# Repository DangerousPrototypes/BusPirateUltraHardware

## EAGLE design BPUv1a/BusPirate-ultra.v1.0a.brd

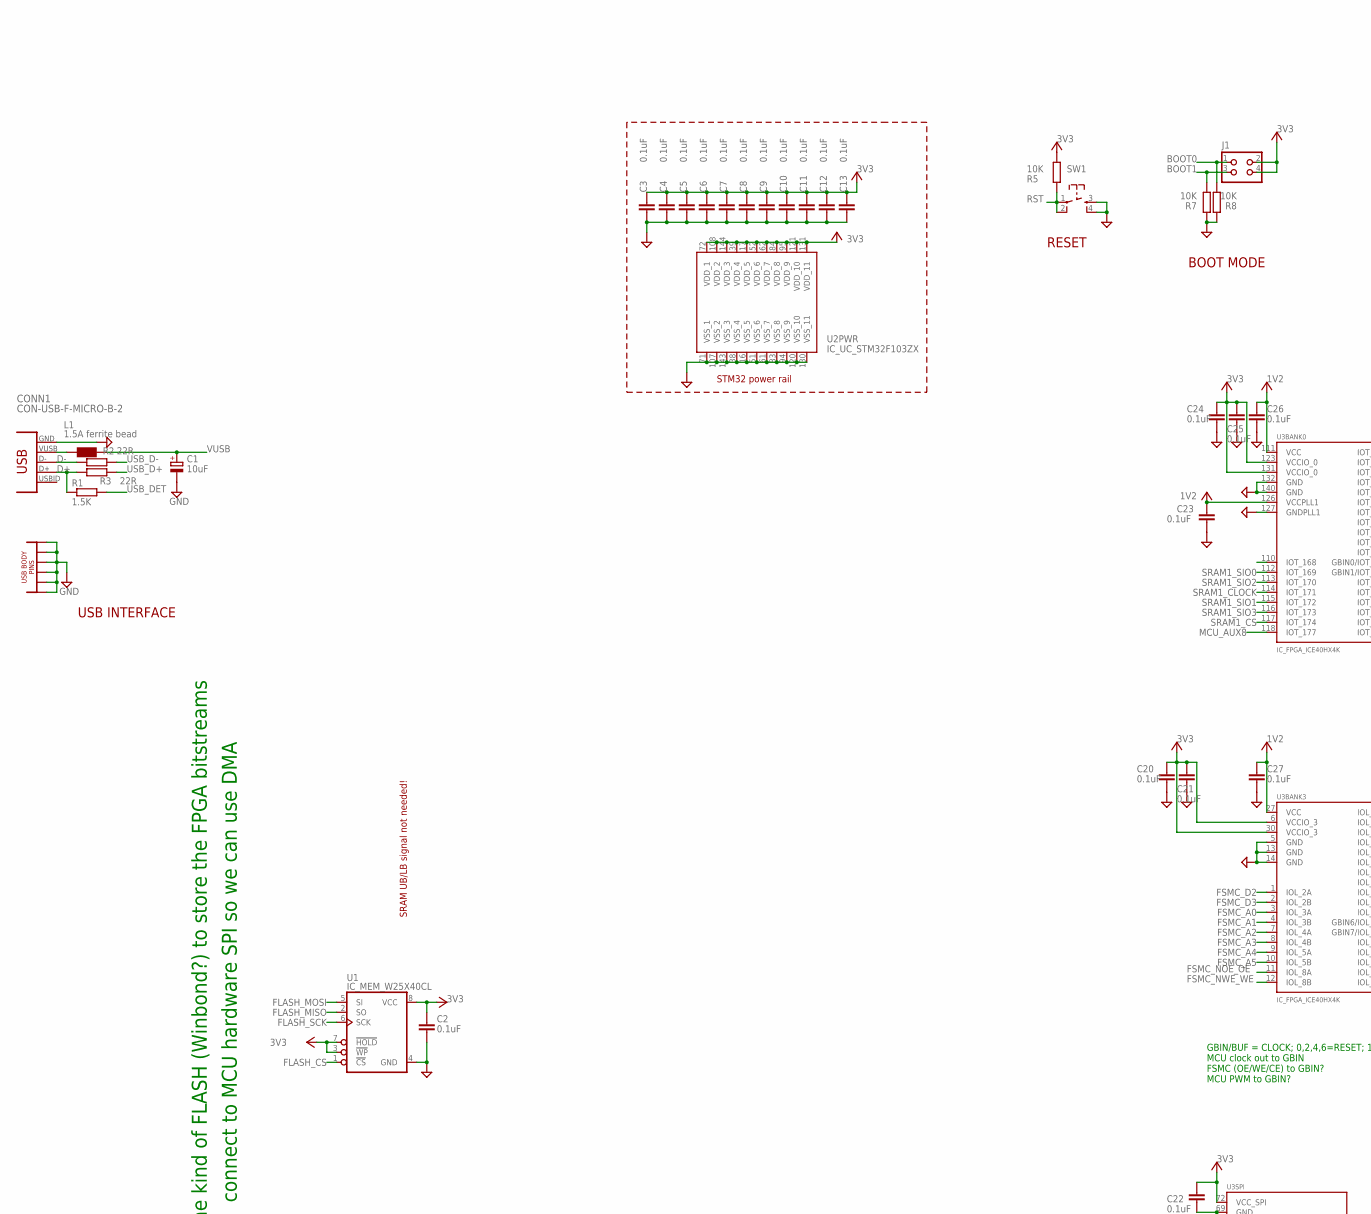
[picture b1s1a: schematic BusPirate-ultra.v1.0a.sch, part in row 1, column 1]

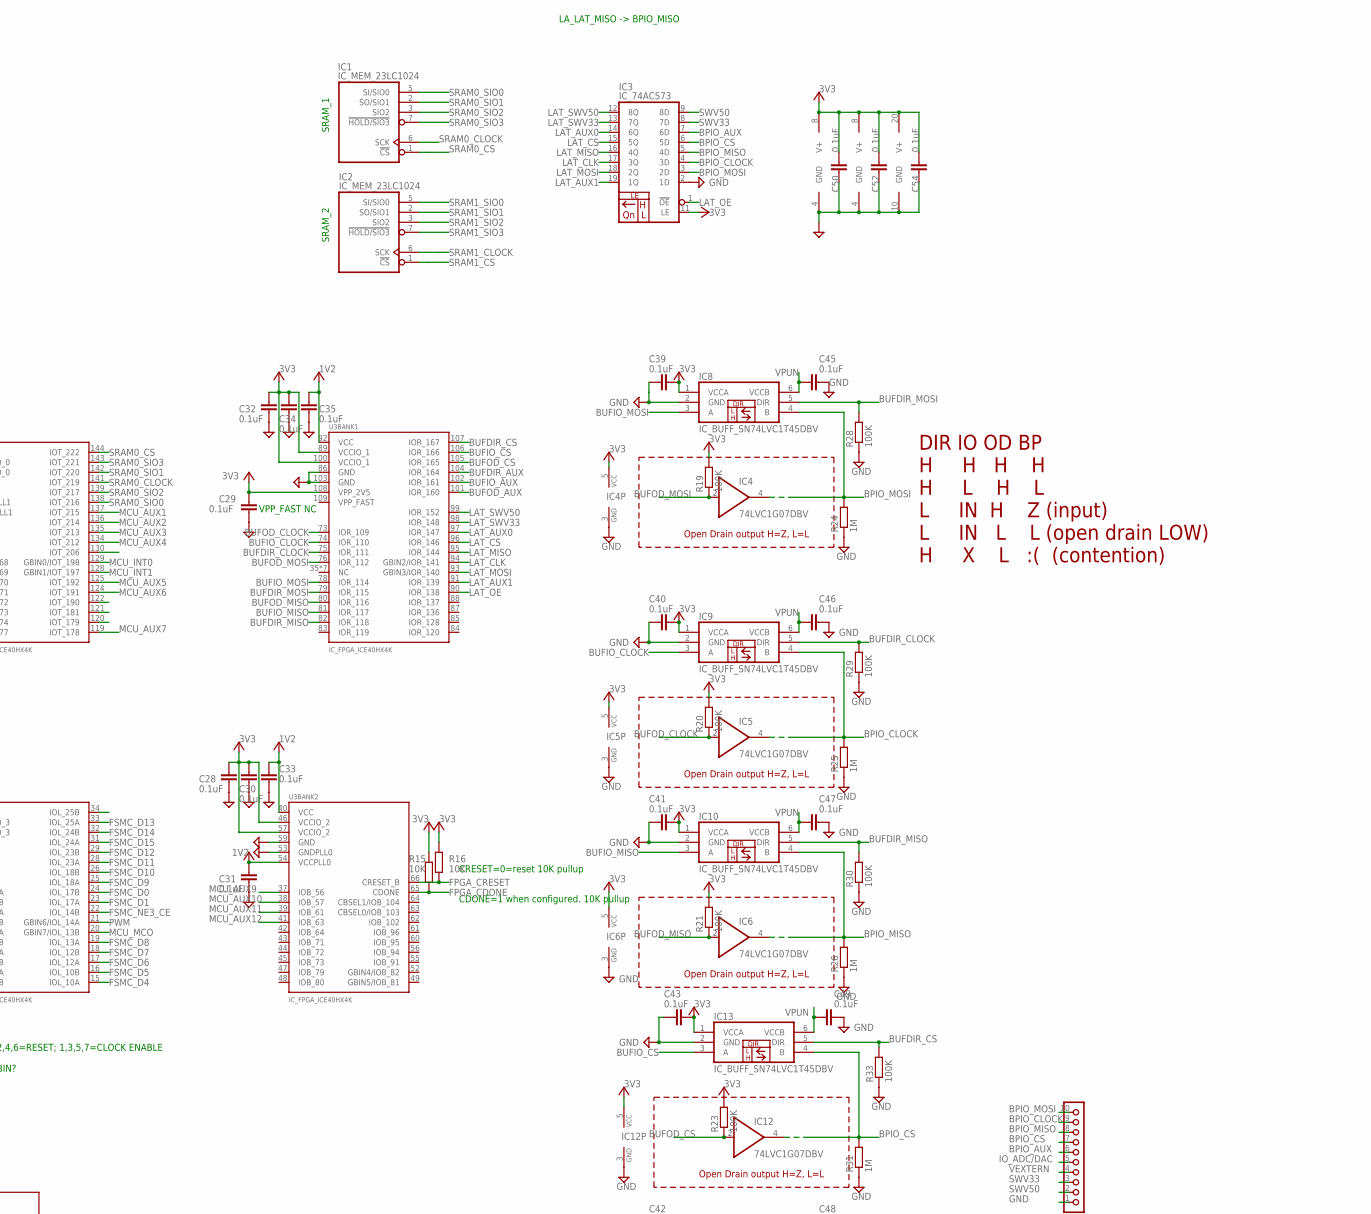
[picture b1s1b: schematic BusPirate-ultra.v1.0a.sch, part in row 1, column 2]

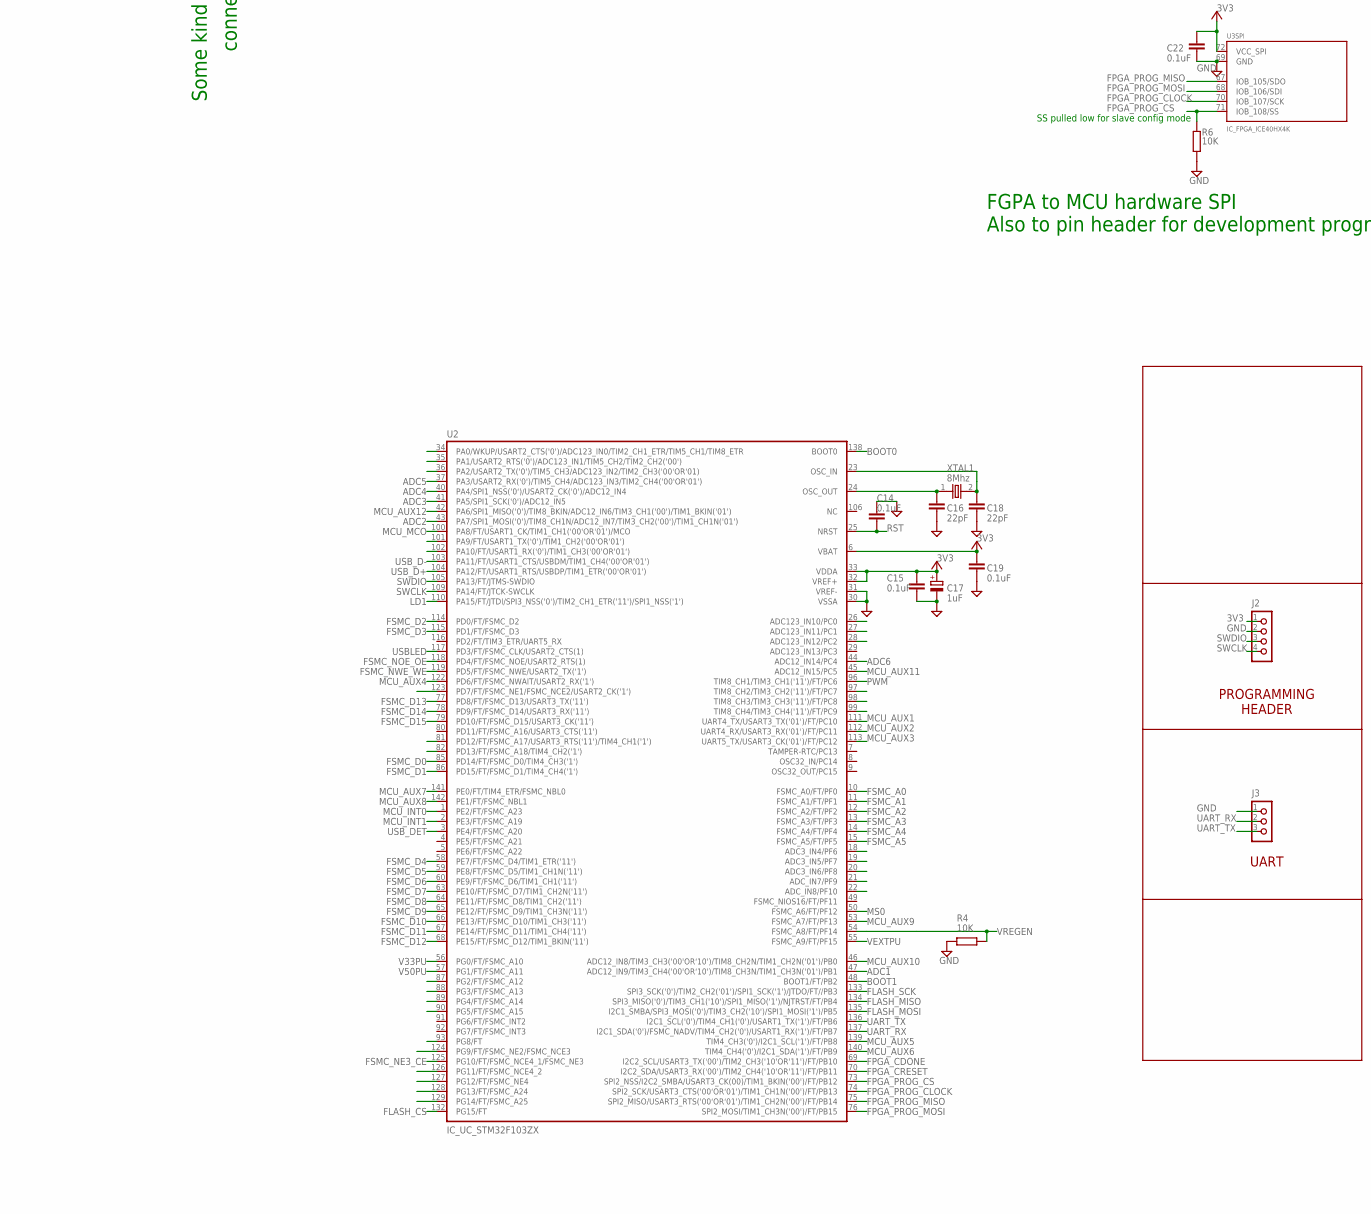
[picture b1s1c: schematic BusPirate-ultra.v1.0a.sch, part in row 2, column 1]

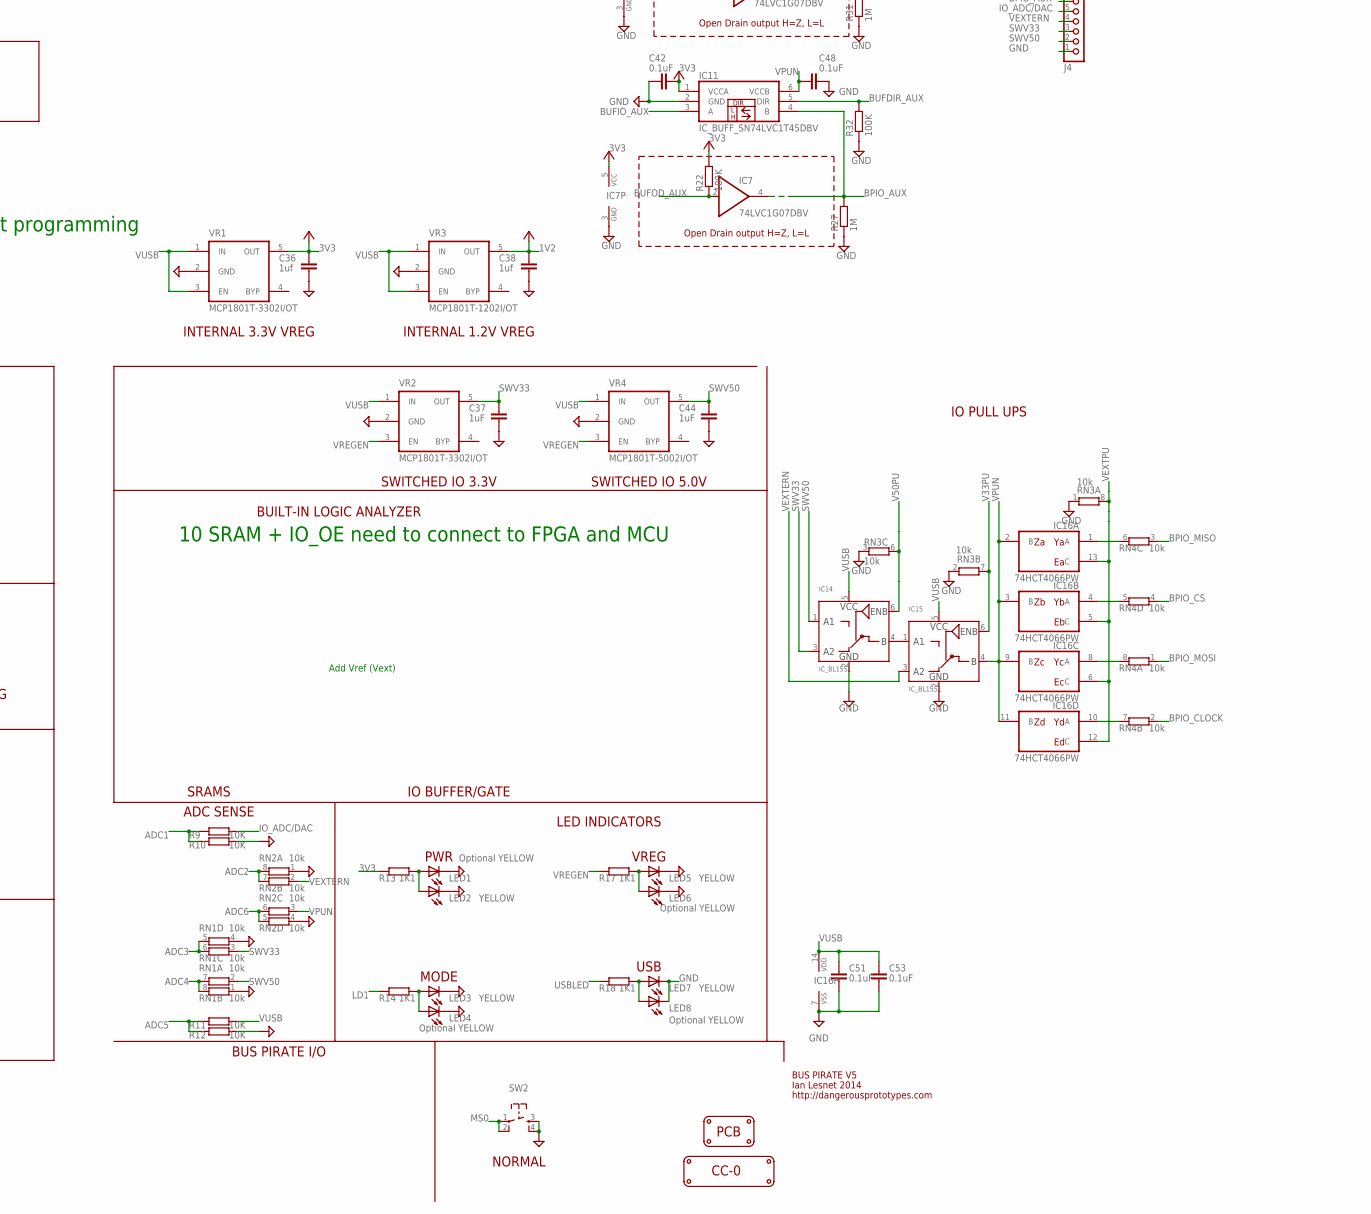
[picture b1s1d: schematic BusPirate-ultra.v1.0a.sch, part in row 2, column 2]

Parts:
C1: 10uF; SMC_A
C2, C3, C4, C5, C6, C7, C8, C9, C11, C12, C13, C14, C15, C19, C21, C22, C23, C24, C25, C26, C28, C29, C30, C31, C32, C33, C34, C35, C39, C40, C41, C42, C43, C45, C46, C47, C48, C49, C50, C51, C52, C53, C54: 0.1uF; C0603
C10, C20, C27: 0.1uF; C402
C16, C18: 22pF; C0603
C17: 1uF; SMC_A
C36, C38: 1uf; C0603
C37, C44: 1uF; C0603
CONN1: CON-USB-F-MICRO-B-2; CON_USB_MICRO-B-2-SD-47589-001
IC1, IC2: IC_MEM_23LC1024; SOIC-8
IC3: IC_74AC573; TSSOP-20
IC4, IC5, IC6, IC7, IC12: 74LVC1G07DBV; SOT23-5
IC8, IC9, IC10, IC11, IC13: IC_BUFF_SN74LVC1T45DBV; DBV-R-PDSO-G6
IC14, IC15: IC_BL1551; SC-70-6
IC16: 74HCT4066PW; 40XX_TSSOP14
J1: CON_HEADER_2X02-PTH; M2X2
J2: CON_HEADER_1X04; M1X4
J3: CON_HEADER_1X03-PTH; M1X3
J4: CON_HEADER_1X10-RIGHT_ANGLED_PTH_SHROUDED; M1X10_MALE_RIGHT_ANGLES_PTH_SHROUDED
L1: 1.5A ferrite bead; WE-KI_0805_B
LED1, LED4, LED6, LED8: Optional YELLOW; LED-805
LED2, LED3, LED5, LED7: YELLOW; LED-805
LOGO1: LOGO_CC-0
PCB1: PCB_DP_RECTANGLE-50X100; DP10050_V1
R1: 1.5K; R603
R2, R3: 22R; R603
R4, R5, R6: 10K; R603
R7, R8, R9, R10, R11, R12, R15, R16: 10K; R0603
R13, R14, R17, R18: 1K1; R603
R19, R20, R21, R22, R23, R28, R29, R30, R32, R33: 100K; R0603
R24, R25, R26, R27, R31: 1M; R0603
RN1, RN2, RN3, RN4: 10k; RN8P-4R-CRA06S
SW1, SW2: SW_TACT_4P; SW_TACT_SMALL
U1: IC_MEM_W25X40CL; SOIC-8
U2: IC_UC_STM32F103ZX; TQFP-144
U3: IC_FPGA_ICE40HX4K; TQFP-144
VR1, VR2: MCP1801T-3302I/OT; SOT-23-5@1
VR3: MCP1801T-1202I/OT; SOT-23-5@1
VR4: MCP1801T-5002I/OT; SOT-23-5@1
XTAL1: 8Mhz; XTAL_4X6

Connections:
1V2: C23.2, C26.2, C27.1, C31.2, C33.2, C35.2, C38.1, U3.27 (VCC), U3.40 (VCC), U3.54 (VCCPLL0), U3.92 (VCC), U3.111 (VCC), U3.126 (VCCPLL1), VR3.5 (OUT)
3V3: C2.2, C3.2, C4.2, C5.2, C6.2, C7.2, C8.2, C9.2, C10.1, C11.2, C12.2, C13.2, C15.2, C17.+, C19.2, C20.1, C21.2, C22.2, C24.2, C25.2, C28.2, C29.2, C30.2, C32.2, C34.2, C36.1, C39.1, C40.1, C41.1, C42.1, C43.1, C50.1, C52.1, C54.1, IC1.8 (V+), IC2.8 (V+), IC3.11 (LE), IC3.20 (V+), IC4.5 (VCC), IC5.5 (VCC), IC6.5 (VCC), IC7.5 (VCC), IC8.1 (VCCA), IC9.1 (VCCA), IC10.1 (VCCA), IC11.1 (VCCA), IC12.5 (VCC), IC13.1 (VCCA), J1.2, J1.4, J2.1, R5.2, R13.2, R15.2, R16.2, R19.2, R20.2, R21.2, R22.2, R23.2, U1.3 (!WP), U1.7 (!HOLD), U1.8 (VCC), U2.6 (VBAT), U2.17 (VDD_5), U2.32 (VREF+), U2.33 (VDDA), U2.39 (VDD_4), U2.52 (VDD_6), U2.62 (VDD_7), U2.72 (VDD_1), U2.84 (VDD_8), U2.95 (VDD_9), U2.108 (VDD_2), U2.121 (VDD_10), U2.131 (VDD_11), U2.144 (VDD_3), U3.6 (VCCIO_3), U3.30 (VCCIO_3), U3.46 (VCCIO_2), U3.57 (VCCIO_2), U3.72 (VCC_SPI), U3.89 (VCCIO_1), U3.100 (VCCIO_1), U3.108 (VPP_2V5), U3.123 (VCCIO_0), U3.131 (VCCIO_0), VR1.5 (OUT)
ADC1: R9.2, R10.2, U2.47 (ADC12_IN9/TIM3_CH4('00'OR'10')/TIM8_CH3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)
ADC2: RN2.7 (2), RN2.8 (2), U2.43 (PA7/SPI1_MOSI('0')/TIM8_CH1N/ADC12_IN7/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)
ADC3: RN1.5 (2), RN1.6 (2), U2.41 (PA5/SPI1_SCK('0')/ADC12_IN5)
ADC4: RN1.7 (2), RN1.8 (2), U2.40 (PA4/SPI1_NSS('0')/USART2_CK('0')/ADC12_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)
ADC5: R11.2, R12.2, U2.37 (PA3/USART2_RX('0')/TIM5_CH4/ADC123_IN3/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)
ADC6: RN2.5 (2), RN2.6 (2), U2.44 (ADC12_IN14/PC4)
BOOT0: J1.1, R8.1, U2.138 (BOOT0)
BOOT1: J1.3, R7.1, U2.48 (BOOT1/FT/PB2)
BPIO_AUX: IC3.7 (6D), IC7.4 (O), IC11.4 (B), J4.6, R27.2
BPIO_CLOCK: IC3.4 (3D), IC5.4 (O), IC9.4 (B), J4.9, R25.2, RN4.2 (1)
BPIO_CS: IC3.6 (5D), IC12.4 (O), IC13.4 (B), J4.7, R31.2, RN4.4 (1)
BPIO_MISO: IC3.5 (4D), IC6.4 (O), IC10.4 (B), J4.8, R26.2, RN4.3 (1)
BPIO_MOSI: IC3.3 (2D), IC4.4 (O), IC8.4 (B), J4.10, R24.2, RN4.1
BUFDIR_AUX: IC11.5 (DIR), R32.2, U3.104 (IOR_164)
BUFDIR_CLOCK: IC9.5 (DIR), R29.2, U3.75 (IOR_111)
BUFDIR_CS: IC13.5 (DIR), R33.2, U3.107 (IOR_167)
BUFDIR_MISO: IC10.5 (DIR), R30.2, U3.82 (IOR_118)
BUFDIR_MOSI: IC8.5 (DIR), R28.2, U3.79 (IOR_115)
BUFIO_AUX: IC11.3 (A), U3.102 (IOR_161)
BUFIO_CLOCK: IC9.3 (A), U3.74 (IOR_110)
BUFIO_CS: IC13.3 (A), U3.106 (IOR_166)
BUFIO_MISO: IC10.3 (A), U3.81 (IOR_117)
BUFIO_MOSI: IC8.3 (A), U3.78 (IOR_114)
BUFOD_AUX: IC7.2 (I), R22.1, U3.101 (IOR_160)
BUFOD_CLOCK: IC5.2 (I), R20.1, U3.73 (IOR_109)
BUFOD_CS: IC12.2 (I), R23.1, U3.105 (IOR_165)
BUFOD_MISO: IC6.2 (I), R21.1, U3.80 (IOR_116)
BUFOD_MOSI: IC4.2 (I), R19.1, U3.76 (IOR_112)
D+: CONN1.P3 (D+), R1.1, R3.2
D-: CONN1.P2 (D-), R2.2
EXVUSB: CONN1.P1 (VUSB), L1.2 (1)
FLASH_CS: U1.1 (!CS), U2.132 (PG15/FT)
FLASH_MISO: U1.2 (SO), U2.134 (SPI3_MISO('0')/TIM3_CH1('10')/SPI1_MISO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)
FLASH_MOSI: U1.5 (SI), U2.135 (I2C1_SMBA/SPI3_MOSI('0')/TIM3_CH2('10')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)
FLASH_SCK: U1.6 (SCK), U2.133 (SPI3_SCK('0')/TIM2_CH2('01')/SPI1_SCK('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)
FPGA_CDONE: R15.1, U2.69 (I2C2_SCL/USART3_TX('00')/TIM2_CH3('10'O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), U3.65 (CDONE)
FPGA_CRESET: R16.1, U2.70 (I2C2_SDA/USART3_RX('00')/TIM2_CH4('10'O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), U3.66 (CRESET_B)
FPGA_PROG_CLOCK: U2.74 (SPI2_SCK/USART3_CTS('00'OR'01')/TIM1_CH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), U3.70 (IOB_107/SCK)
FPGA_PROG_CS: R6.1, U2.73 (SPI2_NSS/I2C2_SMBA/USART3_CK(00)/TIM1_B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), U3.71 (IOB_108/SS)
FPGA_PROG_MISO: U2.75 (SPI2_MISO/USART3_RTS('00'OR'01')/TIM1_C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), U3.67 (IOB_105/SDO)
FPGA_PROG_MOSI: U2.76 (SPI2_MOSI/TIM1_CH3N('00')/FT/PB15), U3.68 (IOB_106/SDI)
FSMC_A0: U2.10 (FSMC_A0/FT/PF0), U3.3 (IOL_3A)
FSMC_A1: U2.11 (FSMC_A1/FT/PF1), U3.4 (IOL_3B)
FSMC_A2: U2.12 (FSMC_A2/FT/PF2), U3.7 (IOL_4A)
FSMC_A3: U2.13 (FSMC_A3/FT/PF3), U3.8 (IOL_4B)
FSMC_A4: U2.14 (FSMC_A4/FT/PF4), U3.9 (IOL_5A)
FSMC_A5: U2.15 (FSMC_A5/FT/PF5), U3.10 (IOL_5B)
FSMC_D0: U2.85 (PD14/FT/FSMC_D0/TIM4_CH3('1')), U3.24 (IOL_17B)
FSMC_D1: U2.86 (PD15/FT/FSMC_D1/TIM4_CH4('1')), U3.23 (IOL_17A)
FSMC_D2: U2.114 (PD0/FT/FSMC_D2), U3.1 (IOL_2A)
FSMC_D3: U2.115 (PD1/FT/FSMC_D3), U3.2 (IOL_2B)
FSMC_D4: U2.58 (PE7/FT/FSMC_D4/TIM1_ETR('11')), U3.15 (IOL_10A)
FSMC_D5: U2.59 (PE8/FT/FSMC_D5/TIM1_CH1N('11')), U3.16 (IOL_10B)
FSMC_D6: U2.60 (PE9/FT/FSMC_D6/TIM1_CH1('11')), U3.17 (IOL_12A)
FSMC_D7: U2.63 (PE10/FT/FSMC_D7/TIM1_CH2N('11')), U3.18 (IOL_12B)
FSMC_D8: U2.64 (PE11/FT/FSMC_D8/TIM1_CH2('11')), U3.19 (IOL_13A)
FSMC_D9: U2.65 (PE12/FT/FSMC_D9/TIM1_CH3N('11')), U3.25 (IOL_18A)
FSMC_D10: U2.66 (PE13/FT/FSMC_D10/TIM1_CH3('11')), U3.26 (IOL_18B)
FSMC_D11: U2.67 (PE14/FT/FSMC_D11/TIM1_CH4('11')), U3.28 (IOL_23A)
FSMC_D12: U2.68 (PE15/FT/FSMC_D12/TIM1_BKIN('11')), U3.29 (IOL_23B)
FSMC_D13: U2.77 (PD8/FT/FSMC_D13/USART3_TX('11')), U3.33 (IOL_25A)
FSMC_D14: U2.78 (PD9/FT/FSMC_D14/USART3_RX('11')), U3.32 (IOL_24B)
FSMC_D15: U2.79 (PD10/FT/FSMC_D15/USART3_CK('11')), U3.31 (IOL_24A)
FSMC_NE3_CE: U2.125 (PG10/FT/FSMC_NCE4_1/FSMC_NE3), U3.22 (IOL_14B)
FSMC_NOE_OE: U2.118 (PD4/FT/FSMC_NOE/USART2_RTS(1)), U3.11 (IOL_8A)
FSMC_NWE_WE: U2.119 (PD5/FT/FSMC_NWE/USART2_TX('1')), U3.12 (IOL_8B)
GND: C1.-, C2.1, C3.1, C4.1, C5.1, C6.1, C7.1, C8.1, C9.1, C10.2, C11.1, C12.1, C13.1, C14.1, C15.1, C16.1, C17.-, C18.1, C19.1, C20.2, C21.1, C22.1, C23.1, C24.1, C25.1, C26.1, C27.2, C28.1, C29.1, C30.1, C31.1, C32.1, C33.1, C34.1, C35.1, C36.2, C37.2, C38.2, C39.2, C40.2, C41.2, C42.2, C43.2, C44.2, C45.1, C46.1, C47.1, C48.1, C49.1, C50.2, C51.2, C52.2, C53.2, C54.2, CONN1.BODY@1, CONN1.BODY@2, CONN1.BODY@3, CONN1.BODY@4, CONN1.BODY@5, CONN1.BODY@6, CONN1.BODY@7, CONN1.BODY@8, CONN1.BODY@9, CONN1.BODY@10, CONN1.P5 (GND), IC1.4 (GND), IC2.4 (GND), IC3.2 (1D), IC3.10 (GND), IC4.3 (GND), IC5.3 (GND), IC6.3 (GND), IC7.3 (GND), IC8.2 (GND), IC9.2 (GND), IC10.2 (GND), IC11.2 (GND), IC12.3 (GND), IC13.2 (GND), IC14.2 (GND), IC15.2 (GND), IC16.7 (VSS), J2.2, J3.1, J4.1, LED1.C, LED2.C, LED3.C, LED4.C, LED5.C, LED6.C, LED7.C, LED8.C, R4.2, R6.2, R7.2, R8.2, R10.1, R12.1, R24.1, R25.1, R26.1, R27.1, R28.1, R29.1, R30.1, R31.1, R32.1, R33.1, RN1.1, RN1.4 (1), RN2.1, RN2.4 (1), RN3.1, RN3.2 (1), RN3.3 (1), SW1.3, SW1.4, SW2.3, SW2.4, U1.4 (GND), U2.16 (VSS_5), U2.30 (VSSA), U2.31 (VREF-), U2.38 (VSS_4), U2.51 (VSS_6), U2.61 (VSS_7), U2.71 (VSS_1), U2.83 (VSS_8), U2.94 (VSS_9), U2.107 (VSS_2), U2.120 (VSS_10), U2.130 (VSS_11), U2.143 (VSS_3), U3.5 (GND), U3.13 (GND), U3.14 (GND), U3.53 (GNDPLL0), U3.59 (GND), U3.69 (GND), U3.86 (GND), U3.103 (GND), U3.127 (GNDPLL1), U3.132 (GND), U3.140 (GND), VR1.2 (GND), VR2.2 (GND), VR3.2 (GND), VR4.2 (GND)
IO_ADC/DAC: J4.5, R9.1
LAT_AUX0: IC3.14 (6Q), U3.97 (IOR_147)
LAT_AUX1: IC3.19 (1Q), U3.91 (IOR_139)
LAT_CLK: IC3.17 (3Q), U3.94 (GBIN2/IOR_141)
LAT_CS: IC3.15 (5Q), U3.96 (IOR_146)
LAT_MISO: IC3.16 (4Q), U3.95 (IOR_144)
LAT_MOSI: IC3.18 (2Q), U3.93 (GBIN3/IOR_140)
LAT_OE: IC3.1 (!OE), U3.90 (IOR_138)
LAT_SWV33: IC3.13 (7Q), U3.98 (IOR_148)
LAT_SWV50: IC3.12 (8Q), U3.99 (IOR_152)
LD1: R14.2, U2.110 (PA15/FT/JTDI/SPI3_NSS('0')/TIM2_CH1_ETR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)
MCU_AUX1: U2.111 (UART4_TX/USART3_TX('01')/FT/PC10), U3.137 (IOT_215)
MCU_AUX2: U2.112 (UART4_RX/USART3_RX('01')/FT/PC11), U3.136 (IOT_214)
MCU_AUX3: U2.113 (UART5_TX/USART3_CK('01')/FT/PC12), U3.135 (IOT_213)
MCU_AUX4: U2.122 (PD6/FT/FSMC_NWAIT/USART2_RX('1')), U3.134 (IOT_212)
MCU_AUX5: U2.139 (TIM4_CH3('0')/I2C1_SCL('1')/FT/PB8), U3.125 (IOT_192)
MCU_AUX6: U2.140 (TIM4_CH4('0')/I2C1_SDA('1')/FT/PB9), U3.124 (IOT_191)
MCU_AUX7: U2.141 (PE0/FT/TIM4_ETR/FSMC_NBL0), U3.119 (IOT_178)
MCU_AUX8: U2.142 (PE1/FT/FSMC_NBL1), U3.118 (IOT_177)
MCU_AUX9: U2.53 (FSMC_A7/FT/PF13), U3.37 (IOB_56)
MCU_AUX10: U2.46 (ADC12_IN8/TIM3_CH3('00'OR'10')/TIM8_CH2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), U3.38 (IOB_57)
MCU_AUX11: U2.45 (ADC12_IN15/PC5), U3.39 (IOB_61)
MCU_AUX12: U2.42 (PA6/SPI1_MISO('0')/TIM8_BKIN/ADC12_IN6/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), U3.41 (IOB_63)
MCU_INT0: U2.1 (PE2/FT/FSMC_A23), U3.129 (GBIN0/IOT_198)
MCU_INT1: U2.2 (PE3/FT/FSMC_A19), U3.128 (GBIN1/IOT_197)
MCU_MCO: U2.100 (PA8/FT/USART1_CK/TIM1_CH1('00'OR'01')/M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), U3.20 (GBIN7/IOL_13B)
MS0: SW2.1, SW2.2, U2.50 (FSMC_A6/FT/PF12)
unnamed: IC14.4 (B), IC15.1 (A1)
unnamed: IC16.1 (A), RN4.6 (2)
unnamed: IC16.4 (A), RN4.5 (2)
unnamed: IC16.8 (A), RN4.8 (2)
unnamed: IC16.10 (A), RN4.7 (2)
unnamed: LED3.A, LED4.A, R14.1
unnamed: LED1.A, LED2.A, R13.1
unnamed: C18.2, U2.23 (OSC_IN), XTAL1.2
unnamed: C16.2, U2.24 (OSC_OUT), XTAL1.1
unnamed: LED7.A, LED8.A, R18.1
unnamed: LED5.A, LED6.A, R17.1
PWM: U2.96 (TIM8_CH1/TIM3_CH1('11')/FT/PC6), U3.21 (GBIN6/IOL_14A)
RST: C14.2, R5.1, SW1.1, SW1.2, U2.25 (NRST)
SRAM0_CLOCK: IC1.6 (SCK), U3.141 (IOT_219)
SRAM0_CS: IC1.1 (!CS), U3.144 (IOT_222)
SRAM0_SIO0: IC1.5 (SI/SIO0), U3.138 (IOT_216)
SRAM0_SIO1: IC1.2 (SO/SIO1), U3.142 (IOT_220)
SRAM0_SIO2: IC1.3 (SIO2), U3.139 (IOT_217)
SRAM0_SIO3: IC1.7 (!HOLD/SIO3), U3.143 (IOT_221)
SRAM1_CLOCK: IC2.6 (SCK), U3.114 (IOT_171)
SRAM1_CS: IC2.1 (!CS), U3.117 (IOT_174)
SRAM1_SIO0: IC2.5 (SI/SIO0), U3.112 (IOT_169)
SRAM1_SIO1: IC2.2 (SO/SIO1), U3.115 (IOT_172)
SRAM1_SIO2: IC2.3 (SIO2), U3.113 (IOT_170)
SRAM1_SIO3: IC2.7 (!HOLD/SIO3), U3.116 (IOT_173)
SWCLK: J2.4, U2.109 (PA14/FT/JTCK-SWCLK)
SWDIO: J2.3, U2.105 (PA13/FT/JTMS-SWDIO)
SWV33: C37.1, IC3.8 (7D), IC14.3 (A2), J4.3, RN1.3 (1), VR2.5 (OUT)
SWV50: C44.1, IC3.9 (8D), IC14.1 (A1), J4.2, RN1.2 (1), VR4.5 (OUT)
UART_RX: J3.2, U2.137 (I2C1_SDA('0')/FSMC_NADV/TIM4_CH2('0')/U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)
UART_TX: J3.3, U2.136 (I2C1_SCL('0')/TIM4_CH1('0')/USART1_TX('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)
USBLED: R18.2, U2.117 (PD3/FT/FSMC_CLK/USART2_CTS(1))
USB_D+: R3.1, U2.104 (PA12/FT/USART1_RTS/USBDP/TIM1_ETR('00'O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)
USB_D-: R2.1, U2.103 (PA11/FT/USART1_CTS/USBDM/TIM1_CH4('00'O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)
USB_DET: R1.2, U2.3 (PE4/FT/FSMC_A20)
V33PU: IC15.6 (ENB), RN3.7 (2), U2.56 (PG0/FT/FSMC_A10)
V50PU: IC14.6 (ENB), RN3.6 (2), U2.57 (PG1/FT/FSMC_A11)
VEXTERN: IC15.3 (A2), J4.4, RN2.2 (1)
VEXTPU: IC16.5 (C), IC16.6 (C), IC16.12 (C), IC16.13 (C), RN3.8 (2), U2.55 (FSMC_A9/FT/PF15)
VPP_FAST: U3.109 (VPP_FAST)
VPUN: C45.2, C46.2, C47.2, C48.2, C49.2, IC8.6 (VCCB), IC9.6 (VCCB), IC10.6 (VCCB), IC11.6 (VCCB), IC13.6 (VCCB), IC15.4 (B), IC16.2 (B), IC16.3 (B), IC16.9 (B), IC16.11 (B), RN2.3 (1)
VREGEN: R4.1, R17.2, U2.54 (FSMC_A8/FT/PF14), VR2.3 (EN), VR4.3 (EN)
VUSB: C1.+, C51.1, C53.1, IC14.5 (VCC), IC15.5 (VCC), IC16.14 (VDD), L1.1 (2), R11.1, VR1.1 (IN), VR1.3 (EN), VR2.1 (IN), VR3.1 (IN), VR3.3 (EN), VR4.1 (IN)

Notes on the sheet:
BUS PIRATE V5
Ian Lesnet 2014
http://dangerousprototypes.com
SRAMS
IO BUFFER/GATE
BUS PIRATE I/O
BOOT MODE
PWR
MODE
VREG
PROGRAMMING HEADER
USB
INTERNAL 3.3V VREG
SWITCHED IO 3.3V
SWITCHED IO 5.0V
BUILT-IN LOGIC ANALYZER
ADC SENSE
USB INTERFACE
NORMAL
RESET
IO PULL UPS
LED INDICATORS
UART
SRAM UB/LB signal not needed!
Open Drain output H=Z, L=L
10 SRAM + IO_OE need to connect to FPGA and MCU
Some kind of FLASH (Winbond?) to store the FPGA bitstreams
connect to MCU hardware SPI so we can use DMA
FGPA to MCU hardware SPI Also to pin header for development programming
SS pulled low for slave config mode
CDONE=1 when configured. 10K pullup
CRESET=0=reset 10K pullup
VPP_FAST NC
GBIN/BUF = CLOCK; 0,2,4,6=RESET; 1,3,5,7=CLOCK ENABLE MCU clock out to GBIN FSMC (OE/WE/CE) to GBIN? MCU PWM to GBIN?
Add Vref (Vext)
DIR IO OD BP H H H H H L H L L IN H Z (input) L IN L L (open drain LOW) H X L :( (contention)
STM32 power rail
INTERNAL 1.2V VREG
SRAM_1
SRAM_2

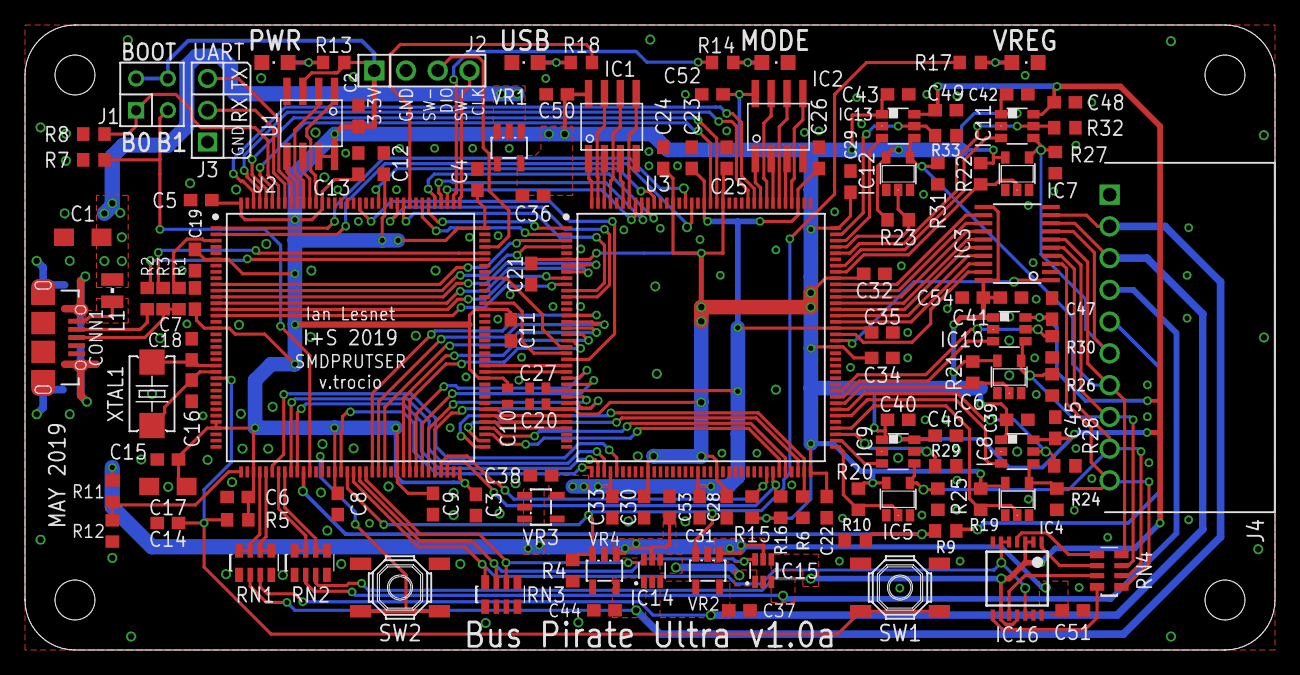
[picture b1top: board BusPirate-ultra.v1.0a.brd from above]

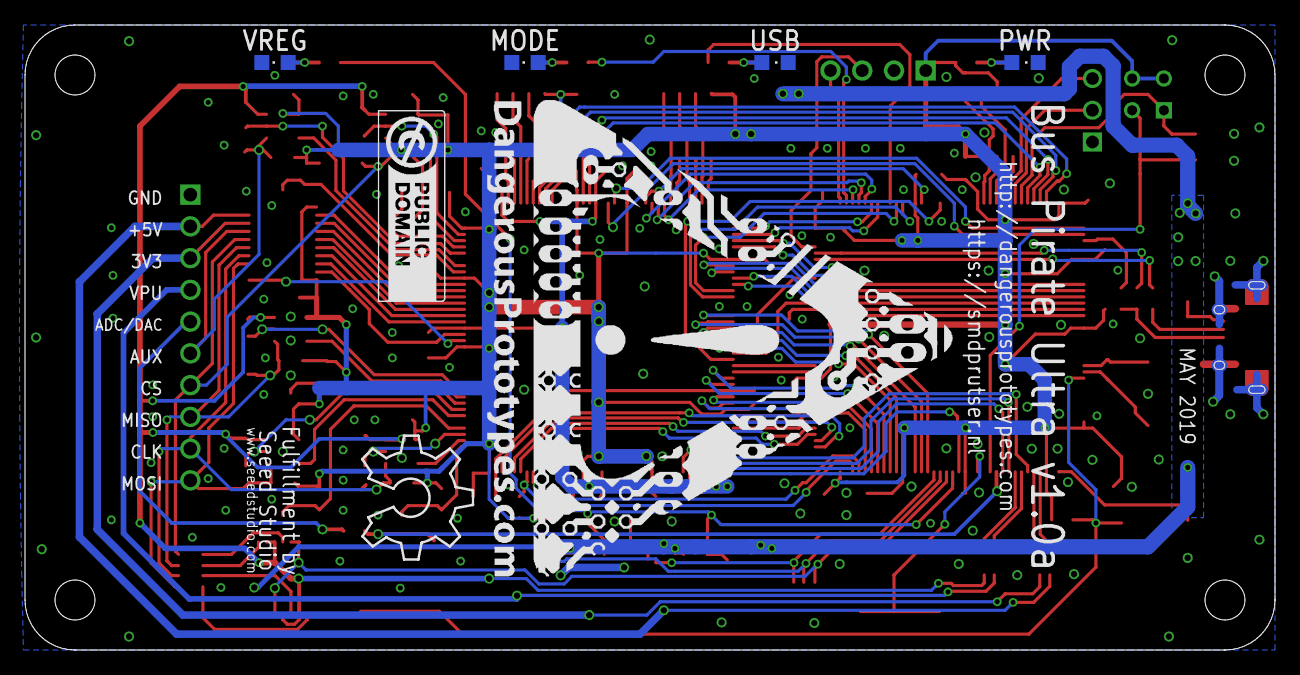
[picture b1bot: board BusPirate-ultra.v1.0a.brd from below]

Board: 2 copper layers, 100.0 x 50.0 mm, 136 parts (7 on the bottom side), 138 nets.

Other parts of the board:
U$1: DP-LOGO
U$2: OSHW_8X350_NOTEXT
U$4: DP_LOGO_ART_1.5X1.5
